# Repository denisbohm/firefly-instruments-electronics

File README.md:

# firefly-instruments-electronics
Firefly Design Test &amp; Programming Instruments Electronics

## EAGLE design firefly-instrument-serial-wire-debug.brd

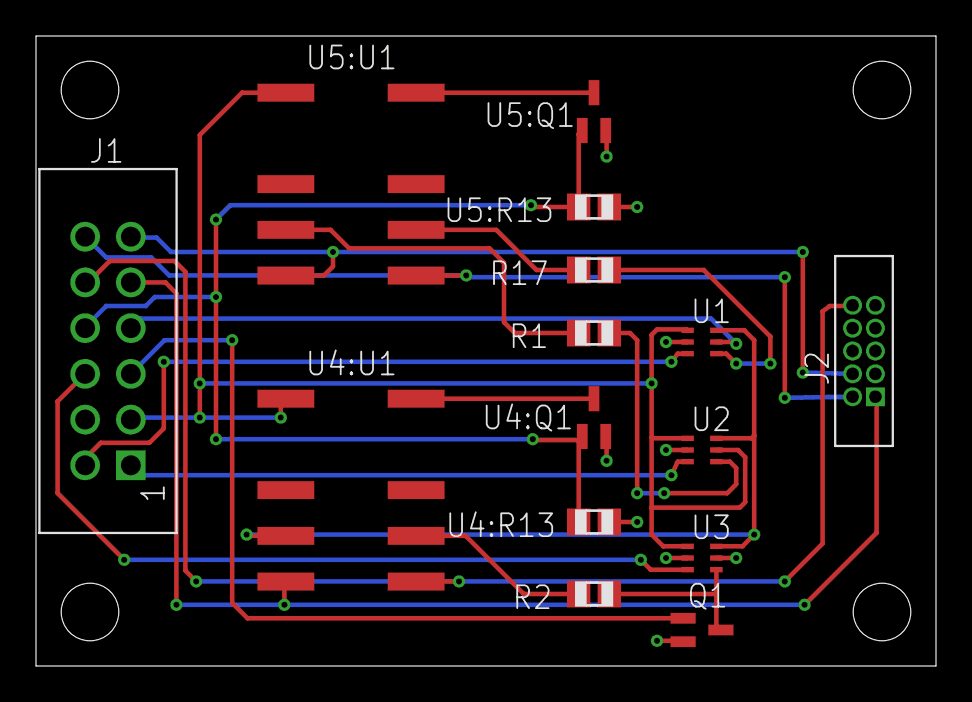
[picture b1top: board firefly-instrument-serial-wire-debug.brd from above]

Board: 2 copper layers, 50.0 x 35.0 mm, 15 parts (0 on the bottom side), 21 nets.

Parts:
J1: CON-12CON-HEADER-2X6; CON-HEADER-2X6
J2: CON-10SWD; SWD-10
Q1: FET-NMCPH3; MCPH3
R1, R2, R17: 240; R0805
U1, U2, U3: 74LVCH1T45; SOT363
U4:Q1, U5:Q1: FET-NMCPH3; MCPH3
U4:R13, U5:R13: 10K; R0805
U4:U1, U5:U1: TXS2SA

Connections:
!DUT_RESET: J1.10, J2.10, U4:U1.8
!INT_RESET: R2.2, U4:U1.9
!RESET: J1.5, Q1.1
!RESET_SENSE: J1.6, U3.3
+3V3: J1.3, U1.1, U2.1, U2.5, U3.1, U4:U1.1, U5:U1.1
DIR_TO_DUT: J1.7, U1.5
DUT_SWDCLK: J1.11, J2.4, U5:U1.5
DUT_SWDIO: J1.12, J2.2, U5:U1.8
DUT_VCC: J1.9, J2.1, U4:U1.5
EN: J1.8, U4:Q1.1, U4:R13.2, U5:Q1.1, U5:R13.2
GND: J1.4, J2.3, J2.5, Q1.2, U1.2, U2.2, U3.2, U3.5, U4:Q1.2, U4:R13.1, U5:Q1.2, U5:R13.1
INT_SWDCLK: R1.2, U5:U1.4
INT_SWDIO: R17.2, U5:U1.9
INT_VCC: U1.6, U2.6, U3.6, U4:U1.4
unnamed: Q1.3, R2.1, U3.4
unnamed: R17.1, U1.4
unnamed: R1.1, U2.4
SWDCLK: J1.1, U2.3
SWDIO: J1.2, U1.3
U4:N$2: U4:Q1.3, U4:U1.12
U5:N$2: U5:Q1.3, U5:U1.12

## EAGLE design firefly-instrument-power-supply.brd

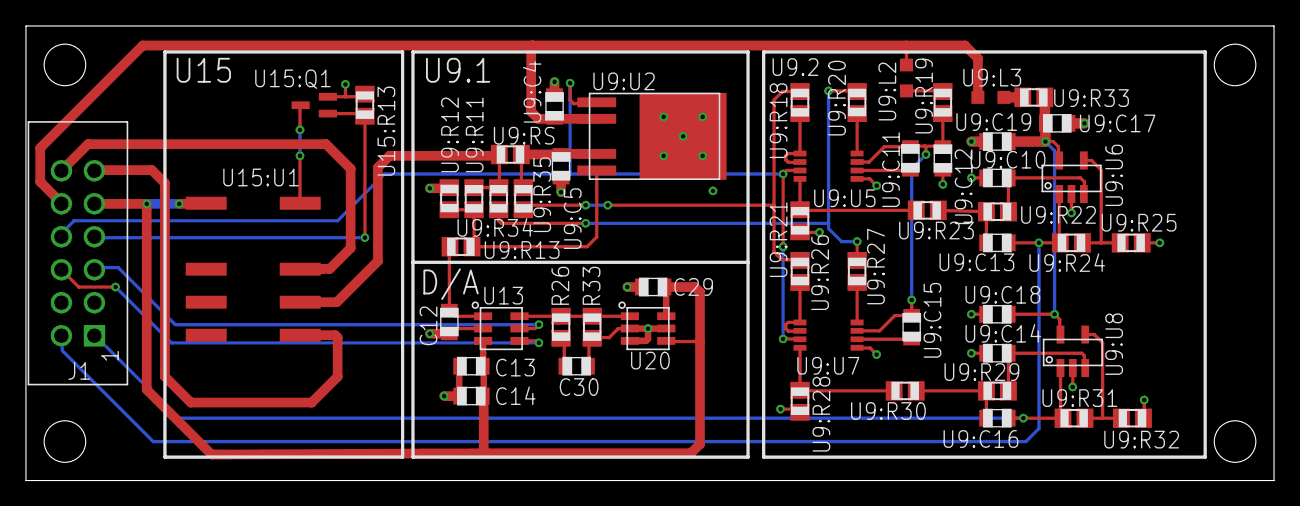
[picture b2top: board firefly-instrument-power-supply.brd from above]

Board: 2 copper layers, 96.1 x 35.0 mm, 54 parts (0 on the bottom side), 38 nets.

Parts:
C12, C13: 100nF; C0805
C14: 10uF; C0805
C29, C30: 2.2uF; C0805
J1: CON-12CON-HEADER-2X6; CON-HEADER-2X6
R26: 43; R0805
R33: 1k; R0805
U9:C4, U9:C5, U9:C17: 1uF; C0805
U9:C10, U9:C13, U9:C14, U9:C16: 1nF; C0805
U9:C11, U9:C15, U9:C18, U9:C19: 100nF; C0805
U9:C12: 10uF; C0805
U9:L2, U9:L3: 1k; L2012C
U9:R11: 650K; R0805
U9:R12, U9:R13: 100K; R0805
U9:R18: 1.8K; R0805
U9:R19, U9:R27, U9:R31, U9:R34, U9:R35: 0; R0805
U9:R20: 43; R0805
U9:R21: 12K; R0805
U9:R22, U9:R23, U9:R29, U9:R30: 10k; R0805
U9:R24: 376; R0805
U9:R25, U9:R32: 1K; R0805
U9:R26, U9:RS: 4.7; R0805
U9:R28, U15:R13: 10K; R0805
U9:R33: 1; R0805
U9:U2: VREG-ADJLDFMPT-TR; PPAK
U9:U5, U9:U7: LTC6102-1MS8; MSOP8
U9:U6, U9:U8: TLV271SN2T1G; SOT-23-5
U13: MCP47X6; SOT-23-6
U15:Q1: FET-NMCPH3; MCPH3
U15:U1: TXS2SA
U20: MCP1501; SOT-23-6

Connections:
+3V3: C13.1, C14.1, C29.1, J1.9, U13.3, U15:U1.1, U20.4, U20.6
+5V9: J1.10, U9:C4.1, U9:L2.1, U9:L3.1, U9:U2.2
ADJ: C12.1, U9:R13.1, U13.1
EN: J1.8, U9:U2.1, U9:U5.3, U9:U7.3
GND: C12.2, C13.2, C14.2, C29.2, C30.2, J1.3, J1.4, R33.2, U9:C4.2, U9:C5.2, U9:C10.2, U9:C12.2, U9:C14.2, U9:C17.2, U9:C18.2, U9:C19.2, U9:R12.1, U9:R21.2, U9:R25.2, U9:R28.2, U9:R32.2, U9:U2.TAB, U9:U5.5, U9:U6.2, U9:U7.5, U9:U8.2, U13.2, U15:Q1.2, U15:R13.1, U20.2, U20.3, U20.5
I2C_SCL: J1.5, U13.5
I2C_SDA: J1.6, U13.4
unnamed: R26.1, R33.1, U13.6, U20.1
unnamed: C30.1, R26.2
SEL: J1.7, U15:Q1.1, U15:R13.2
SHR: J1.2, U9:C13.1, U9:R24.2, U9:U6.1
SLR: J1.1, U9:C16.1, U9:R31.2, U9:U8.1
U9:N$4: U9:R11.1, U9:R12.2, U9:R13.2, U9:U2.5
U9:N$13: U9:L2.2, U9:R19.2
U9:N$14: U9:C11.1, U9:U5.6
U9:N$15: U9:R18.1, U9:U5.1, U9:U5.2
U9:N$16: U9:R20.2, U9:U5.8
U9:N$17: U9:R21.1, U9:R23.1, U9:U5.4
U9:N$18: U9:C13.2, U9:R22.1, U9:R23.2
U9:N$19: U9:C10.1, U9:R22.2, U9:U6.3
U9:N$20: U9:R24.1, U9:R25.1, U9:U6.4
U9:N$21: U9:C15.1, U9:U7.6
U9:N$22: U9:R26.1, U9:U7.1, U9:U7.2
U9:N$23: U9:R27.2, U9:U7.8
U9:N$24: U9:R28.1, U9:R30.1, U9:U7.4
U9:N$25: U9:C16.2, U9:R29.1, U9:R30.2
U9:N$26: U9:C14.1, U9:R29.2, U9:U8.3
U9:N$27: U9:R31.1, U9:R32.1, U9:U8.4
U9:N$28: U9:L3.2, U9:R33.2
U9:N$35: U9:C5.1, U9:R35.2, U9:RS.1, U9:U2.4
U9:SENSE_R: U9:R18.2, U9:R26.2, U9:R35.1
U9:SENSE_S: U9:R20.1, U9:R27.1, U9:R34.1
U9:VCSA: U9:C11.2, U9:C12.1, U9:C15.2, U9:R19.1, U9:U5.7, U9:U7.7
U9:VOA: U9:C17.1, U9:C18.1, U9:C19.1, U9:R33.1, U9:U6.5, U9:U8.5
U15:N$2: U15:Q1.3, U15:U1.12
VADJ: U9:R11.2, U9:R34.2, U9:RS.2, U15:U1.9
VADJ_NC: J1.12, U15:U1.10
VADJ_NO: J1.11, U15:U1.8

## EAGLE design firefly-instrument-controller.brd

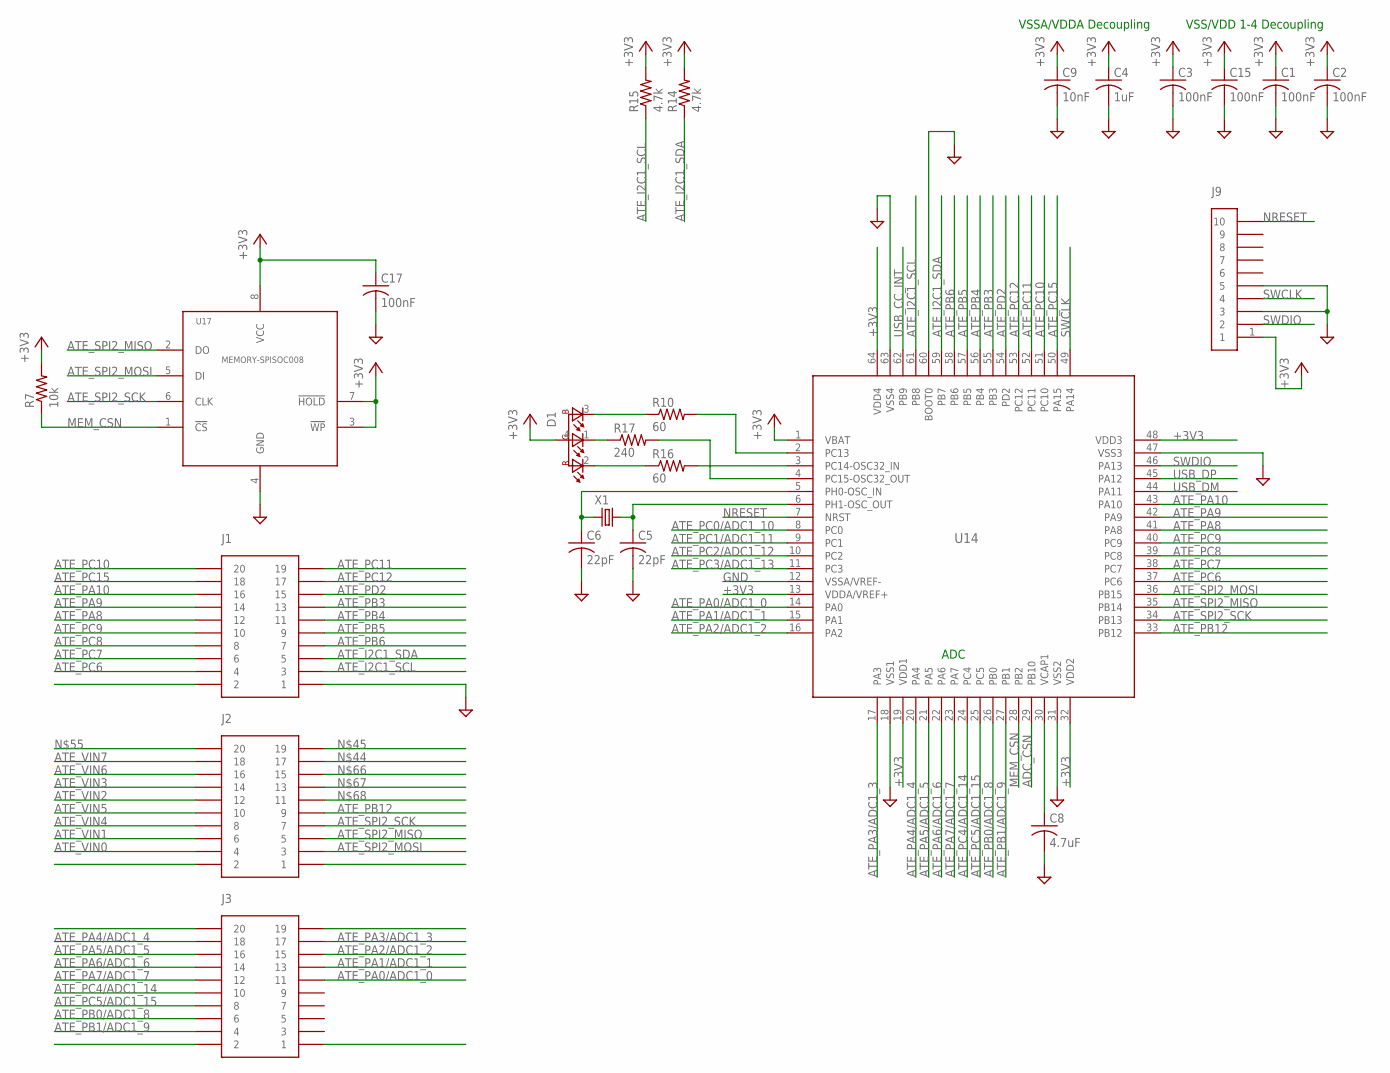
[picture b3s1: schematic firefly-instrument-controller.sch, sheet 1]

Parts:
C1, C2, C3, C15, C17: 100nF; C0805
C4: 1uF; C0805
C5, C6: 22pF; C0805
C8: 4.7uF; C0805
C9: 10nF; C0805
D1: LED-RGB-CAMSL0201RGB; MSL0201RGB
J1, J2, J3: CON-200.05"; CON-HEADER-2X10-0.05
J9: CON-10SWD; SWD-10
R7: 10k; R0805
R10, R16: 60; R0805
R14, R15: 4.7k; R0805
R17: 240; R0805
U14: STM32F411-LQFP64; LQFP-64
U17: MEMORY-SPISOC008; SOC008
X1: XTAL2TXC_7A; TXC_7A

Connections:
+3V3: C1.1, C2.1, C3.1, C4.1, C9.1, C15.1, C17.1, D1.4 (A), J9.1, R7.2, R14.2, R15.2, U14.1 (VBAT), U14.13 (VDDA/VREF+), U14.19 (VDD1), U14.32 (VDD2), U14.48 (VDD3), U14.64 (VDD4), U17.3 (!WP), U17.7 (!HOLD), U17.8 (VCC); also elsewhere on the board
ADC_CSN: U14.29 (PB10); also elsewhere on the board
ATE_I2C1_SCL: J1.3, R15.1, U14.61 (PB8); also elsewhere on the board
ATE_I2C1_SDA: J1.5, R14.1, U14.59 (PB7); also elsewhere on the board
ATE_PA0/ADC1_0: J3.11, U14.14 (PA0)
ATE_PA1/ADC1_1: J3.13, U14.15 (PA1)
ATE_PA2/ADC1_2: J3.15, U14.16 (PA2)
ATE_PA3/ADC1_3: J3.17, U14.17 (PA3)
ATE_PA4/ADC1_4: J3.18, U14.20 (PA4)
ATE_PA5/ADC1_5: J3.16, U14.21 (PA5)
ATE_PA6/ADC1_6: J3.14, U14.22 (PA6)
ATE_PA7/ADC1_7: J3.12, U14.23 (PA7)
ATE_PA8: J1.12, U14.41 (PA8)
ATE_PA9: J1.14, U14.42 (PA9)
ATE_PA10: J1.16, U14.43 (PA10)
ATE_PB0/ADC1_8: J3.6, U14.26 (PB0)
ATE_PB1/ADC1_9: J3.4, U14.27 (PB1)
ATE_PB3: J1.13, U14.55 (PB3)
ATE_PB4: J1.11, U14.56 (PB4)
ATE_PB5: J1.9, U14.57 (PB5)
ATE_PB6: J1.7, U14.58 (PB6)
ATE_PB12: J2.9, U14.33 (PB12)
ATE_PC0/ADC1_10: U14.8 (PC0)
ATE_PC1/ADC1_11: U14.9 (PC1)
ATE_PC2/ADC1_12: U14.10 (PC2)
ATE_PC3/ADC1_13: U14.11 (PC3)
ATE_PC4/ADC1_14: J3.10, U14.24 (PC4)
ATE_PC5/ADC1_15: J3.8, U14.25 (PC5)
ATE_PC6: J1.4, U14.37 (PC6)
ATE_PC7: J1.6, U14.38 (PC7)
ATE_PC8: J1.8, U14.39 (PC8)
ATE_PC9: J1.10, U14.40 (PC9)
ATE_PC10: J1.20, U14.51 (PC10)
ATE_PC11: J1.19, U14.52 (PC11)
ATE_PC12: J1.17, U14.53 (PC12)
ATE_PC15: J1.18, U14.50 (PA15)
ATE_PD2: J1.15, U14.54 (PD2)
ATE_SPI2_MISO: J2.5, U14.35 (PB14), U17.2 (DO); also elsewhere on the board
ATE_SPI2_MOSI: J2.3, U14.36 (PB15), U17.5 (DI); also elsewhere on the board
ATE_SPI2_SCK: J2.7, U14.34 (PB13), U17.6 (CLK); also elsewhere on the board
ATE_VIN0: J2.4; also elsewhere on the board
ATE_VIN1: J2.6; also elsewhere on the board
ATE_VIN2: J2.12; also elsewhere on the board
ATE_VIN3: J2.14; also elsewhere on the board
ATE_VIN4: J2.8; also elsewhere on the board
ATE_VIN5: J2.10; also elsewhere on the board
ATE_VIN6: J2.16; also elsewhere on the board
ATE_VIN7: J2.18; also elsewhere on the board
GND: C1.2, C2.2, C3.2, C4.2, C5.2, C6.2, C8.2, C9.2, C15.2, C17.2, J1.1, J9.3, J9.5, U14.12 (VSSA/VREF-), U14.18 (VSS1), U14.31 (VSS2), U14.47 (VSS3), U14.60 (BOOT0), U14.63 (VSS4), U17.4 (GND); also elsewhere on the board
MEM_CSN: R7.1, U14.28 (PB2), U17.1 (!CS)
unnamed: R10.2, U14.2 (PC13)
unnamed: C5.1, U14.6 (PH1-OSC_OUT), X1.2
unnamed: C6.1, U14.5 (PH0-OSC_IN), X1.1
unnamed: R16.2, U14.3 (PC14-OSC32_IN)
unnamed: D1.1 (G), R17.1
unnamed: D1.2 (R), R16.1
unnamed: C8.1, U14.30 (VCAP1)
unnamed: R17.2, U14.4 (PC15-OSC32_OUT)
unnamed: D1.3 (B), R10.1
NRESET: J9.10, U14.7 (NRST)
SWCLK: J9.4, U14.49 (PA14)
SWDIO: J9.2, U14.46 (PA13)
USB_CC_INT: U14.62 (PB9); also elsewhere on the board
USB_DM: U14.44 (PA11); also elsewhere on the board
USB_DP: U14.45 (PA12); also elsewhere on the board

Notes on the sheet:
ADC
VSSA/VDDA Decoupling
VSS/VDD 1-4 Decoupling

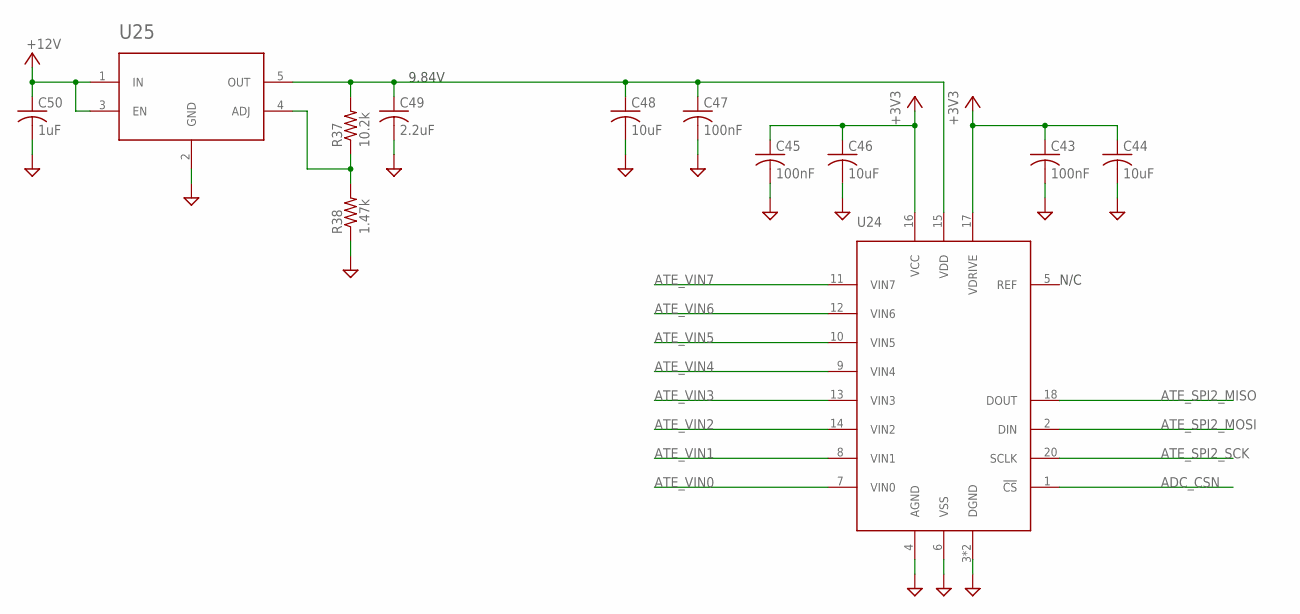
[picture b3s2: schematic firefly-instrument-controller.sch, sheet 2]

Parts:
C43, C45, C47: 100nF; C0805
C44, C46, C48: 10uF; C0805
C49: 2.2uF; C0805
C50: 1uF; C0805
R37: 10.2k; R0805
R38: 1.47k; R0805
U24: AD7327; TSSOP-20
U25: VREG-ADJAP2204; SOT-23-5

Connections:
+3V3: C43.1, C44.1, C45.1, C46.1, U24.16 (VCC), U24.17 (VDRIVE); also elsewhere on the board
+12V: C50.1, U25.1 (IN), U25.3 (EN); also elsewhere on the board
ADC_CSN: U24.1 (!CS); also elsewhere on the board
ATE_SPI2_MISO: U24.18 (DOUT); also elsewhere on the board
ATE_SPI2_MOSI: U24.2 (DIN); also elsewhere on the board
ATE_SPI2_SCK: U24.20 (SCLK); also elsewhere on the board
ATE_VIN0: U24.7 (VIN0); also elsewhere on the board
ATE_VIN1: U24.8 (VIN1); also elsewhere on the board
ATE_VIN2: U24.14 (VIN2); also elsewhere on the board
ATE_VIN3: U24.13 (VIN3); also elsewhere on the board
ATE_VIN4: U24.9 (VIN4); also elsewhere on the board
ATE_VIN5: U24.10 (VIN5); also elsewhere on the board
ATE_VIN6: U24.12 (VIN6); also elsewhere on the board
ATE_VIN7: U24.11 (VIN7); also elsewhere on the board
GND: C43.2, C44.2, C45.2, C46.2, C47.2, C48.2, C49.2, C50.2, R38.1, U24.3 (DGND), U24.4 (AGND), U24.6 (VSS), U24.19 (DGND), U25.2 (GND); also elsewhere on the board
unnamed: C47.1, C48.1, C49.1, R37.2, U24.15 (VDD), U25.5 (OUT)
unnamed: R37.1, R38.2, U25.4 (ADJ)

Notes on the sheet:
9.84V
N/C

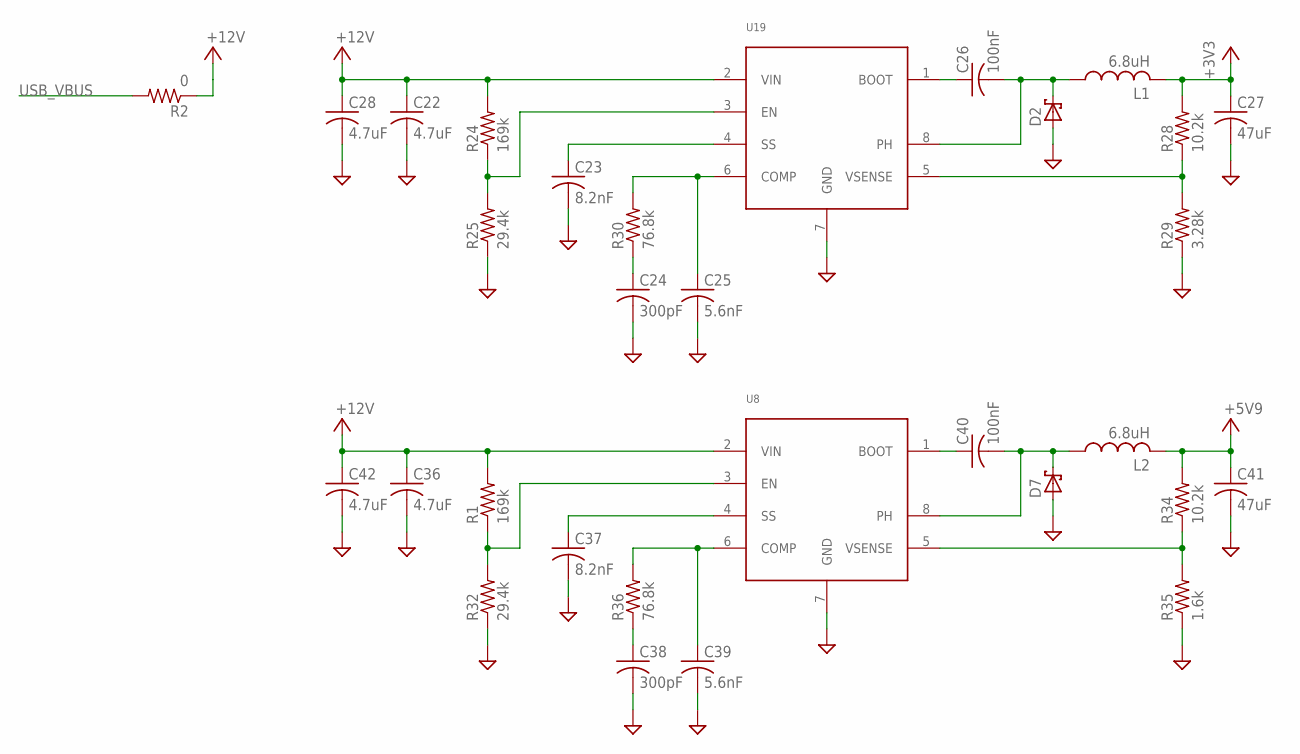
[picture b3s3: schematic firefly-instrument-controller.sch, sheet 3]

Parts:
C22, C28, C36, C42: 4.7uF; C1210
C23, C37: 8.2nF; C0805
C24, C38: 300pF; C0805
C25, C39: 5.6nF; C0805
C26, C40: 100nF; C0805
C27, C41: 47uF; C1206
D2, D7: D-USDO-214AB; DO-214AB
L1, L2: 6.8uH; SDR0805
R1, R24: 169k; R0805
R2: 0; R0805
R25, R32: 29.4k; R0805
R28, R34: 10.2k; R0805
R29: 3.28k; R0805
R30, R36: 76.8k; R0805
R35: 1.6k; R0805
U8, U19: TPS54232; R-PDSO-G8

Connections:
+3V3: C27.1, L1.2, R28.2; also elsewhere on the board
+5V9: C41.1, L2.2, R34.2
+12V: C22.1, C28.1, C36.1, C42.1, R1.2, R2.1, R24.2, U8.2 (VIN), U19.2 (VIN); also elsewhere on the board
GND: C22.2, C23.2, C24.2, C25.2, C27.2, C28.2, C36.2, C37.2, C38.2, C39.2, C41.2, C42.2, D2.A, D7.A, R25.1, R29.1, R32.1, R35.1, U8.7 (GND), U19.7 (GND); also elsewhere on the board
unnamed: C40.1, U8.1 (BOOT)
unnamed: C40.2, D7.C, L2.1, U8.8 (PH)
unnamed: C26.1, U19.1 (BOOT)
unnamed: C26.2, D2.C, L1.1, U19.8 (PH)
unnamed: R28.1, R29.2, U19.5 (VSENSE)
unnamed: C25.1, R30.2, U19.6 (COMP)
unnamed: C24.1, R30.1
unnamed: C23.1, U19.4 (SS)
unnamed: R24.1, R25.2, U19.3 (EN)
unnamed: R34.1, R35.2, U8.5 (VSENSE)
unnamed: C39.1, R36.2, U8.6 (COMP)
unnamed: C38.1, R36.1
unnamed: C37.1, U8.4 (SS)
unnamed: R1.1, R32.2, U8.3 (EN)
USB_VBUS: R2.2; also elsewhere on the board

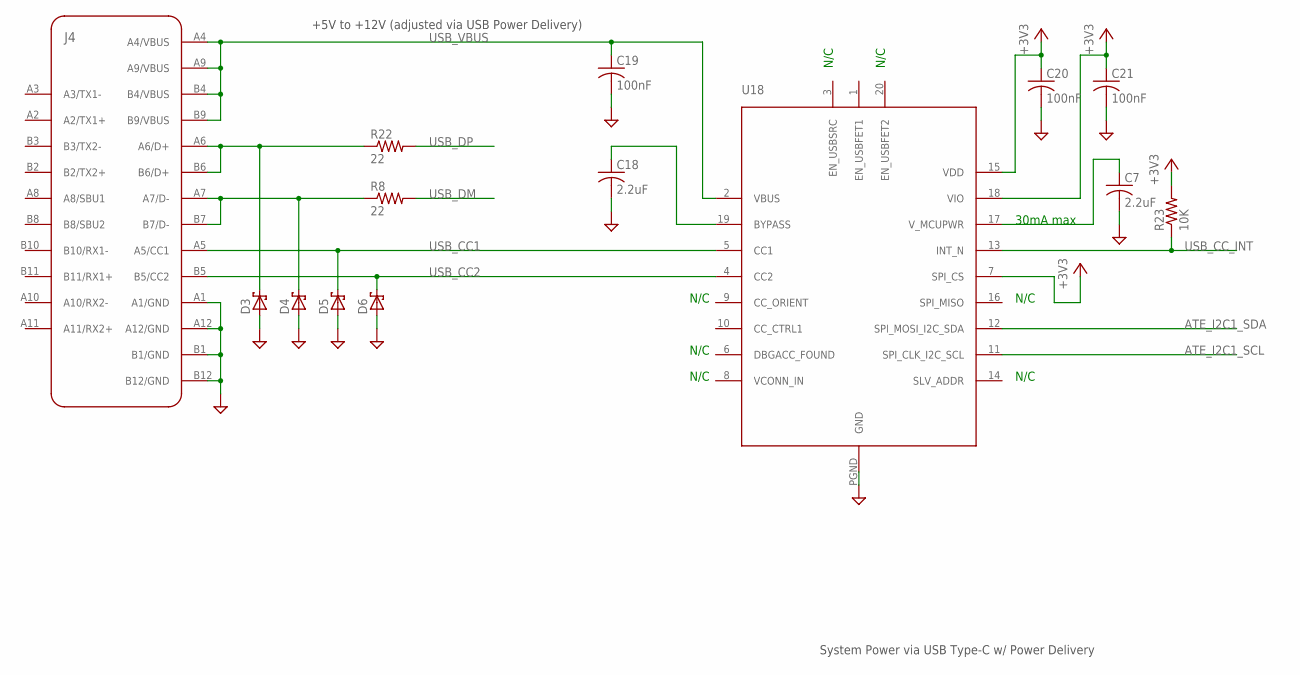
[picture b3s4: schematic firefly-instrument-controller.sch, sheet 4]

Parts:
C7, C18: 2.2uF; C0805
C19, C20, C21: 100nF; C0805
D3, D4, D5, D6: D-USSMM4FXXA; SMM4FXXA
J4: USB-CAUSB1-DFN-PTR3; AUSB1-DFN-PTR3
R8, R22: 22; R0805
R23: 10K; R0805
U18: PTN5100; HVQFN20

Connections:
+3V3: C20.1, C21.1, R23.2, U18.7 (SPI_CS), U18.15 (VDD), U18.18 (VIO); also elsewhere on the board
ATE_I2C1_SCL: U18.11 (SPI_CLK_I2C_SCL); also elsewhere on the board
ATE_I2C1_SDA: U18.12 (SPI_MOSI_I2C_SDA); also elsewhere on the board
GND: C7.2, C18.2, C19.2, C20.2, C21.2, D3.A, D4.A, D5.A, D6.A, J4.A1 (A1/GND), J4.A12 (A12/GND), J4.B1 (B1/GND), J4.B12 (B12/GND), U18.PGND (GND); also elsewhere on the board
unnamed: C18.1, U18.19 (BYPASS)
unnamed: C7.1, U18.17 (V_MCUPWR)
USBC_DM: D4.C, J4.A7 (A7/D-), J4.B7 (B7/D-), R8.1
USBC_DP: D3.C, J4.A6 (A6/D+), J4.B6 (B6/D+), R22.1
USB_CC1: D5.C, J4.A5 (A5/CC1), U18.5 (CC1)
USB_CC2: D6.C, J4.B5 (B5/CC2), U18.4 (CC2)
USB_CC_INT: R23.1, U18.13 (INT_N); also elsewhere on the board
USB_DM: R8.2; also elsewhere on the board
USB_DP: R22.2; also elsewhere on the board
USB_VBUS: C19.1, J4.A4 (A4/VBUS), J4.A9 (A9/VBUS), J4.B4 (B4/VBUS), J4.B9 (B9/VBUS), U18.2 (VBUS); also elsewhere on the board

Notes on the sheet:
N/C
30mA max
System Power via USB Type-C w/ Power Delivery
+5V to +12V (adjusted via USB Power Delivery)

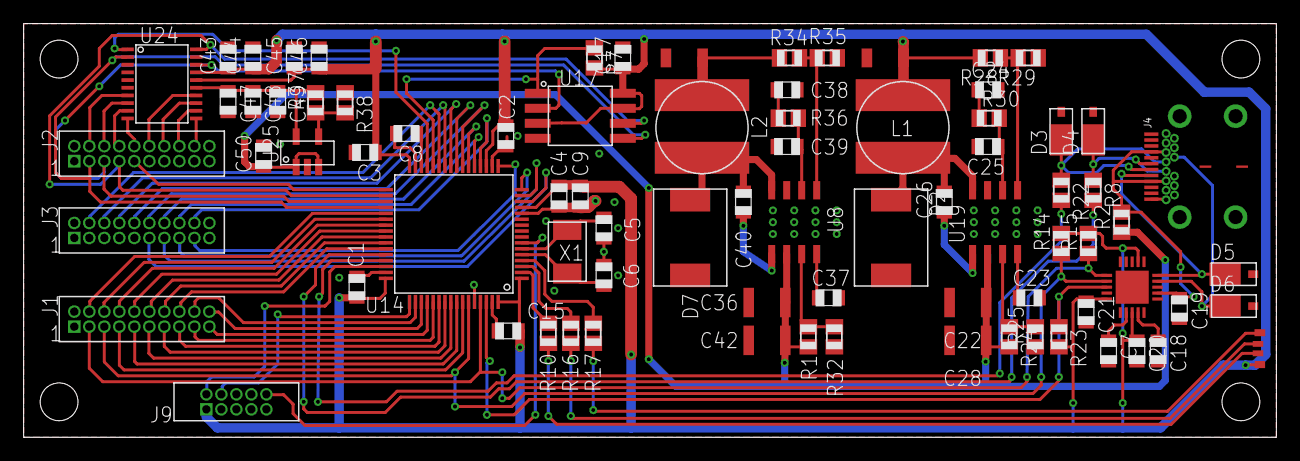
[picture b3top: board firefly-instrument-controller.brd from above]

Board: 2 copper layers, 106.0 x 35.0 mm, 81 parts (0 on the bottom side), 86 nets.

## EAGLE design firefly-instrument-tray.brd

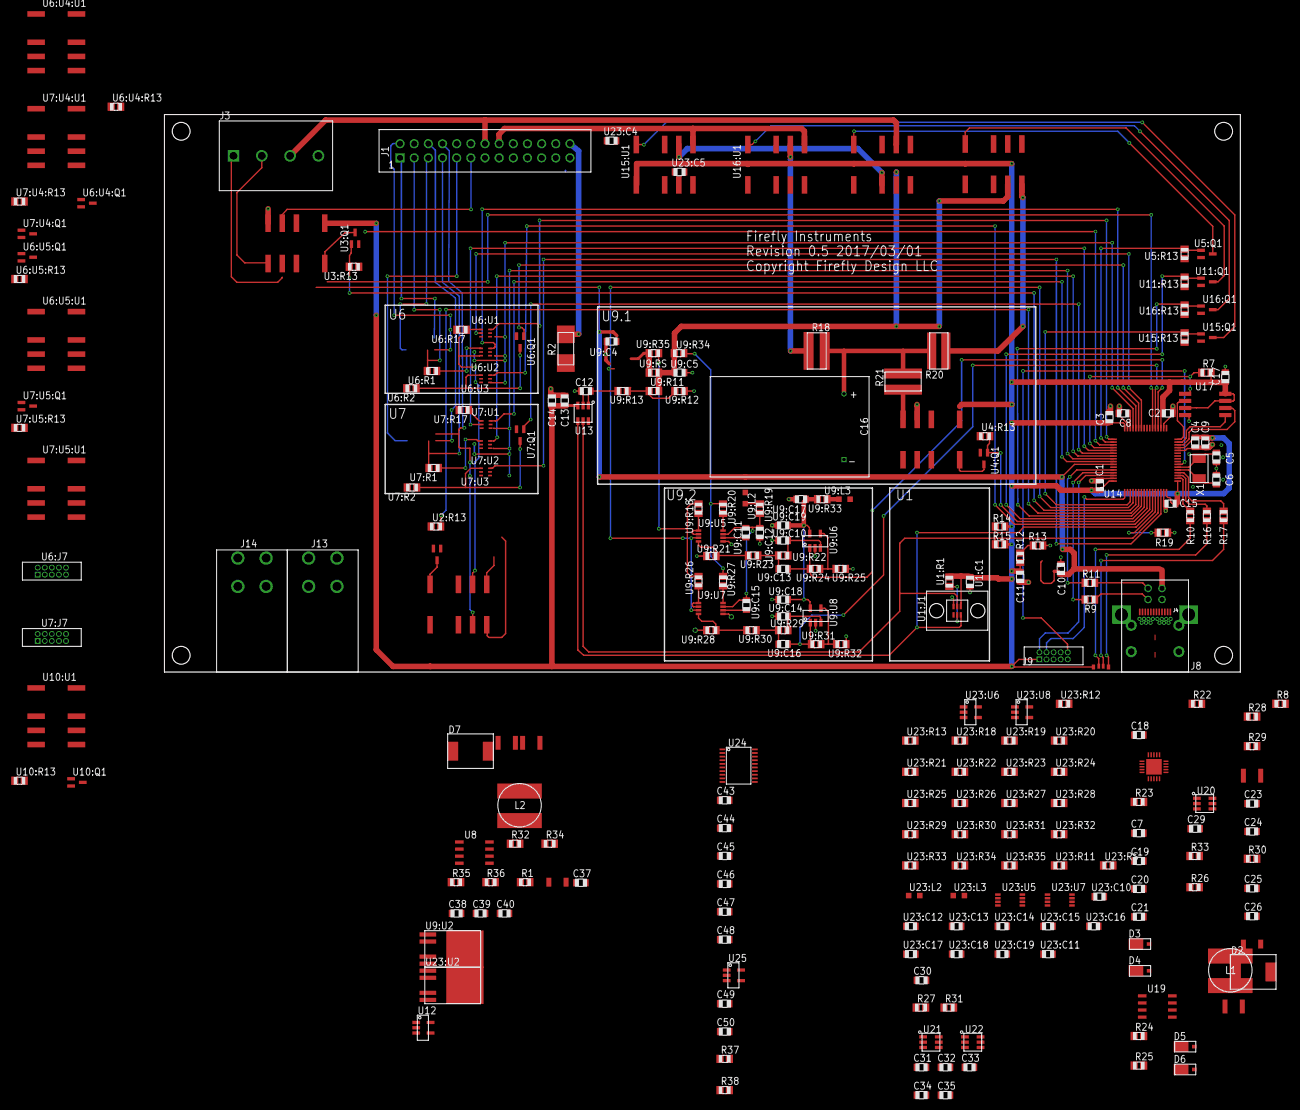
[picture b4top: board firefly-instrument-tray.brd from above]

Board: 2 copper layers, 193.0 x 100.0 mm, 251 parts (0 on the bottom side), 181 nets.

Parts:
C1, C2, C3, C12, C13, C15, C17, C19, C20, C21, C26, C31, C32, C40, C43, C45, C47: 100nF; C0805
C4, C10, C11, C50: 1uF; C0805
C5, C6: 22pF; C0805
C7, C18, C29, C30, C34, C35, C49: 2.2uF; C0805
C8: 4.7uF; C0805
C9: 10nF; C0805
C14, C33, C44, C46, C48: 10uF; C0805
C16: 1F; PM118
C22, C28, C36, C42: 4.7uF; C1210
C23, C37: 8.2nF; C0805
C24, C38: 300pF; C0805
C25, C39: 5.6nF; C0805
C27, C41: 47uF; C1206
D1: LED-RGB-CAMSL0201RGB; MSL0201RGB
D2, D7: D-USDO-214AB; DO-214AB
D3, D4, D5, D6: D-USSMM4FXXA; SMM4FXXA
J1: CON-26; CON-HEADER-2X13
J3: CON-4282847-4; 282847-4
J4: USB-CAUSB1-DFN-PTR3; AUSB1-DFN-PTR3
J8: USB-4PINUSB-B1HSB6; USB-B1HSB6
J9: CON-10SWD; SWD-10
J13, J14: CON-1CT3151; CT3151
L1, L2: 6.8uH; SDR0805
R1, R24: 169k; R0805
R2: 100; RW0S6BB
R7: 10k; R0805
R8, R9, R11, R22: 22; R0805
R10, R16: 60; R0805
R12: 72.5k; R0805
R13, R23: 10K; R0805
R14, R15: 4.7k; R0805
R17: 240; R0805
R18: 1 (2W WW); RCL1225
R19: 0; R0805
R20: 49.9 (2W WW); KRL6432
R21: 49.9 (2W WW); RCL1225
R25, R32: 29.4k; R0805
R26, R31: 43; R0805
R27, R33: 1; R0805
R28, R34, R37: 10.2k; R0805
R29: 3.28k; R0805
R30, R36: 76.8k; R0805
R35: 1.6k; R0805
R38: 1.47k; R0805
U1:C1, U9:C4, U9:C5, U9:C17, U23:C4, U23:C5, U23:C17: 1uF; C0805
U1:J1: SMFLP
U1:R1, U9:R22, U9:R23, U9:R29, U9:R30, U23:R22, U23:R23, U23:R29, U23:R30: 10k; R0805
U1:U1: TCS3471; DFN6
U2:Q1, U3:Q1, U4:Q1, U5:Q1, U6:Q1, U6:U4:Q1, U6:U5:Q1, U7:Q1, U7:U4:Q1, U7:U5:Q1, U10:Q1, U11:Q1, U15:Q1, U16:Q1: FET-NMCPH3; MCPH3
U2:R13, U3:R13, U4:R13, U5:R13, U6:U4:R13, U6:U5:R13, U7:U4:R13, U7:U5:R13, U9:R28, U10:R13, U11:R13, U15:R13, U16:R13, U23:R28: 10K; R0805
U2:U1, U3:U1, U4:U1, U5:U1, U6:U4:U1, U6:U5:U1, U7:U4:U1, U7:U5:U1, U10:U1, U11:U1, U15:U1, U16:U1: TXS2SA
U6:J7, U7:J7: CON-10SWD; SWD-10
U6:R1, U6:R2, U6:R17, U7:R1, U7:R2, U7:R17: 240; R0805
U6:U1, U6:U2, U6:U3, U7:U1, U7:U2, U7:U3: 74LVCH1T45; SOT363
U8, U19: TPS54232; R-PDSO-G8
U9:C10, U9:C13, U9:C14, U9:C16, U23:C10, U23:C13, U23:C14, U23:C16: 1nF; C0805
U9:C11, U9:C15, U9:C18, U9:C19, U23:C11, U23:C15, U23:C18, U23:C19: 100nF; C0805
U9:C12, U23:C12: 10uF; C0805
U9:L2, U9:L3, U23:L2, U23:L3: 1k; L2012C
U9:R11, U23:R11: 650K; R0805
U9:R12, U9:R13, U23:R12, U23:R13: 100K; R0805
U9:R18, U23:R18: 1.8K; R0805
U9:R19, U9:R27, U9:R31, U9:R34, U9:R35, U23:R19, U23:R27, U23:R31, U23:R34, U23:R35: 0; R0805
U9:R20, U23:R20: 43; R0805
U9:R21, U23:R21: 12K; R0805
U9:R24, U23:R24: 376; R0805
U9:R25, U9:R32, U23:R25, U23:R32: 1K; R0805
U9:R26, U9:RS, U23:R26, U23:RS: 4.7; R0805
U9:R33, U23:R33: 1; R0805
U9:U2, U23:U2: VREG-ADJLDFMPT-TR; PPAK
U9:U5, U9:U7, U23:U5, U23:U7: LTC6102-1MS8; MSOP8
U9:U6, U9:U8, U23:U6, U23:U8: TLV271SN2T1G; SOT-23-5
U12: VREG-ADJAP7331-WG-7; SOT-23-5
U13, U21: MCP47X6; SOT-23-6
U14: STM32F411-LQFP64; LQFP-64
U17: MEMORY-SPISOC008; SOC008
U18: PTN5100; HVQFN20
U20, U22: MCP1501; SOT-23-6
U24: AD7327; TSSOP-20
U25: VREG-ADJAP2204; SOT-23-5
X1: XTAL2TXC_7A; TXC_7A

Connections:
+3V3: C1.1, C2.1, C3.1, C4.1, C9.1, C11.1, C13.1, C14.1, C15.1, C17.1, C20.1, C21.1, C27.1, C29.1, C32.1, C33.1, C34.1, C43.1, C44.1, C45.1, C46.1, D1.4, J9.1, L1.2, R7.2, R12.2, R14.2, R15.2, R23.2, R28.2, U1:C1.1, U1:R1.2, U1:U1.1, U2:U1.1, U3:U1.1, U4:U1.1, U5:U1.1, U6:U1.1, U6:U2.1, U6:U2.5, U6:U3.1, U6:U4:U1.1, U6:U5:U1.1, U7:U1.1, U7:U2.1, U7:U2.5, U7:U3.1, U7:U4:U1.1, U7:U5:U1.1, U10:U1.1, U11:U1.1, U12.5, U13.3, U14.1, U14.13, U14.19, U14.32, U14.48, U14.64, U15:U1.1, U16:U1.1, U17.3, U17.7, U17.8, U18.7, U18.15, U18.18, U20.4, U20.6, U21.3, U22.4, U22.6, U24.16, U24.17
+5V9: C41.1, L2.2, R34.2, U9:C4.1, U9:L2.1, U9:L3.1, U9:U2.2, U23:C4.1, U23:L2.1, U23:L3.1, U23:U2.2
+12V: C22.1, C28.1, C36.1, C42.1, C50.1, J13.1, J13.2, J13.3, J13.4, R1.2, R24.2, U8.2, U19.2, U25.1, U25.3
ADC_CSN: U14.43, U24.1
ATE_BAT_ADJ_EN: U14.51, U15:Q1.1, U15:R13.2
ATE_BAT_CAP_EN: U14.55, U16:Q1.1, U16:R13.2
ATE_BS_ADJ: C12.1, U9:R13.1, U13.1
ATE_BS_EN: U9:U2.1, U9:U5.3, U9:U7.3, U14.52
ATE_BS_SHR: U9:C13.1, U9:R24.2, U9:U6.1, U14.20
ATE_BS_SLR: U9:C16.1, U9:R31.2, U9:U8.1, U14.21
ATE_BUTTON+: U10:U1.8, U24.10
ATE_BUTTON_EN: U3:Q1.1, U3:R13.2, U14.53
ATE_DRAIN_EN: U4:Q1.1, U4:R13.2, U14.57
ATE_FILL_EN: U11:Q1.1, U11:R13.2, U14.56
ATE_MCU1_VCC: U2:U1.8, U24.14
ATE_MCU2_VCC: U2:U1.5, U24.13
ATE_SWD1_DIR_TO_DUT: U6:U1.5, U14.26
ATE_SWD1_NRESET: U6:Q1.1, U14.27
ATE_SWD1_PWR: U6:U4:Q1.1, U6:U4:R13.2, U6:U5:Q1.1, U6:U5:R13.2, U14.29
ATE_SWD1_SENSE_NRESET: U6:U3.3, U14.58
ATE_SWD1_SWDCLK: U6:U2.3, U14.28
ATE_SWD1_SWDIO: U6:U1.3, U14.33
ATE_SWD2_DIR_TO_DUT: U7:U1.5, U14.37
ATE_SWD2_NRESET: U7:Q1.1, U14.38
ATE_SWD2_PWR: U7:U4:Q1.1, U7:U4:R13.2, U7:U5:Q1.1, U7:U5:R13.2, U14.40
ATE_SWD2_SENSE_NRESET: U7:U3.3, U14.62
ATE_SWD2_SWDCLK: U7:U2.3, U14.39
ATE_SWD2_SWDIO: U7:U1.3, U14.41
ATE_USB_5V_EN: U5:Q1.1, U5:R13.2, U14.34
ATE_USB_ADJ: C31.1, U21.1, U23:R13.1
ATE_USB_EN: U14.35, U23:U2.1, U23:U5.3, U23:U7.3
ATE_USB_SHR: U14.22, U23:C13.1, U23:R24.2, U23:U6.1
ATE_USB_SLR: U14.23, U23:C16.1, U23:R31.2, U23:U8.1
ATE_VB: U10:U1.5, U24.9
ATE_VSENSE: U2:Q1.1, U2:R13.2, U10:Q1.1, U10:R13.2, U14.54
BATADJ: U9:C5.1, U9:R11.2, U9:R34.2, U9:RS.2, U11:U1.4, U15:U1.9, U24.7
BATCAP: R18.1, U16:U1.9
BATCAPV: C16.+, R18.2, R20.2, R21.2, U24.11
BOOT0: R19.1, U14.60
DRAINCAP: R21.1, U4:U1.5
DUT_BATTERY+: J1.16, U15:U1.8, U16:U1.8
DUT_BUTTON+: J1.11, J3.1, U3:U1.4, U10:U1.9
DUT_BUTTON-: J1.23, J3.2, U3:U1.5
DUT_MCU1_NRESET: J1.5, U6:J7.10, U6:U4:U1.8
DUT_MCU1_SWDCLK: J1.3, U6:J7.4, U6:U5:U1.5
DUT_MCU1_SWDIO: J1.2, U6:J7.2, U6:U5:U1.8
DUT_MCU1_VCC: J1.1, U2:U1.9, U6:J7.1, U6:U4:U1.5
DUT_MCU2_NRESET: J1.9, U7:J7.10, U7:U4:U1.8
DUT_MCU2_SWDCLK: J1.7, U7:J7.4, U7:U5:U1.5
DUT_MCU2_SWDIO: J1.6, U7:J7.2, U7:U5:U1.8
DUT_MCU2_VCC: J1.8, U2:U1.4, U7:J7.1, U7:U4:U1.5
DUT_MOTOR+: J1.26, R2.1
DUT_MOTOR-: J1.25, R2.2
DUT_USB_5V: J1.14, J3.3, U5:U1.9
DUT_VB: J1.15, U10:U1.4
FILLCAP: R20.1, U11:U1.5
GND: C1.2, C2.2, C3.2, C4.2, C5.2, C6.2, C7.2, C8.2, C9.2, C10.2, C11.2, C12.2, C13.2, C14.2, C15.2, C16.-, C17.2, C18.2, C19.2, C20.2, C21.2, C22.2, C23.2, C24.2, C25.2, C27.2, C28.2, C29.2, C30.2, C31.2, C32.2, C33.2, C34.2, C35.2, C36.2, C37.2, C38.2, C39.2, C41.2, C42.2, C43.2, C44.2, C45.2, C46.2, C47.2, C48.2, C49.2, C50.2, D2.A, D3.A, D4.A, D5.A, D6.A, D7.A, J1.4, J1.24, J3.4, J4.A1, J4.A12, J4.B1, J4.B12, J8.4, J9.3, J9.5, J14.1, J14.2, J14.3, J14.4, R13.1, R19.2, R25.1, R27.2, R29.1, R32.1, R33.2, R35.1, R38.1, U1:C1.2, U1:U1.3, U2:Q1.2, U2:R13.1, U3:Q1.2, U3:R13.1, U4:Q1.2, U4:R13.1, U4:U1.4, U5:Q1.2, U5:R13.1, U6:J7.3, U6:J7.5, U6:Q1.2, U6:U1.2, U6:U2.2, U6:U3.2, U6:U3.5, U6:U4:Q1.2, U6:U4:R13.1, U6:U5:Q1.2, U6:U5:R13.1, U7:J7.3, U7:J7.5, U7:Q1.2, U7:U1.2, U7:U2.2, U7:U3.2, U7:U3.5, U7:U4:Q1.2, U7:U4:R13.1, U7:U5:Q1.2, U7:U5:R13.1, U8.7, U9:C4.2, U9:C5.2, U9:C10.2, U9:C12.2, U9:C14.2, U9:C17.2, U9:C18.2, U9:C19.2, U9:R12.1, U9:R21.2, U9:R25.2, U9:R28.2, U9:R32.2, U9:U2.TAB, U9:U5.5, U9:U6.2, U9:U7.5, U9:U8.2, U10:Q1.2, U10:R13.1, U11:Q1.2, U11:R13.1, U12.2, U13.2, U14.12, U14.18, U14.31, U14.47, U14.63, U15:Q1.2, U15:R13.1, U16:Q1.2, U16:R13.1, U17.4, U18.PGND, U19.7, U20.2, U20.3, U20.5, U21.2, U22.2, U22.3, U22.5, U23:C4.2, U23:C5.2, U23:C10.2, U23:C12.2, U23:C14.2, U23:C17.2, U23:C18.2, U23:C19.2, U23:R12.1, U23:R21.2, U23:R25.2, U23:R28.2, U23:R32.2, U23:U2.TAB, U23:U5.5, U23:U6.2, U23:U7.5, U23:U8.2, U24.3, U24.4, U24.6, U24.19, U25.2
I2C_SCL: R15.1, U1:U1.2, U13.5, U14.61, U18.11, U21.5
I2C_SDA: R14.1, U1:U1.6, U13.4, U14.59, U18.12, U21.4
MEM_CSN: R7.1, U14.36, U17.1
unnamed: R10.2, U14.2
unnamed: C40.1, U8.1
unnamed: C40.2, D7.C, L2.1, U8.8
unnamed: C19.1, J4.A4, J4.A9, J4.B4, J4.B9, U18.2
unnamed: C5.1, U14.6, X1.2
unnamed: C6.1, U14.5, X1.1
unnamed: R16.2, U14.3
unnamed: C8.1, U14.30
unnamed: R12.1, R13.2, U12.4
unnamed: J8.2, R11.2
unnamed: R17.2, U14.4
unnamed: J8.3, R9.2
unnamed: D1.3, R10.1
unnamed: D1.1, R16.1
unnamed: D1.2, R17.1
unnamed: D3.C, J4.A6, J4.B6, R22.1
unnamed: D4.C, J4.A7, J4.B7, R8.1
unnamed: D5.C, J4.A5, U18.5
unnamed: D6.C, J4.B5, U18.4
unnamed: R26.1, R33.1, U13.6, U20.1
unnamed: C18.1, U18.19
unnamed: C7.1, U18.17
unnamed: C26.1, U19.1
unnamed: C26.2, D2.C, L1.1, U19.8
unnamed: C30.1, R26.2
unnamed: R28.1, R29.2, U19.5
unnamed: C25.1, R30.2, U19.6
unnamed: C24.1, R30.1
unnamed: C23.1, U19.4
unnamed: R24.1, R25.2, U19.3
unnamed: R27.1, R31.1, U21.6, U22.1
unnamed: C35.1, R31.2
unnamed: R34.1, R35.2, U8.5
unnamed: C39.1, R36.2, U8.6
unnamed: C38.1, R36.1
unnamed: C37.1, U8.4
unnamed: R1.1, R32.2, U8.3
unnamed: C47.1, C48.1, C49.1, R37.2, U24.15, U25.5
unnamed: R37.1, R38.2, U25.4
NRESET: J9.10, U14.7
SPI_MISO: U14.16, U17.2, U24.18
SPI_MOSI: U14.15, U17.5, U24.2
SPI_SCLK: U14.14, U17.6, U24.20
SWCLK: J9.4, U14.49
SWDIO: J9.2, U14.46
U1:INT: U1:R1.1, U1:U1.5
U2:N$2: U2:Q1.3, U2:U1.12
U3:N$2: U3:Q1.3, U3:U1.12
U4:N$2: U4:Q1.3, U4:U1.12
U5:N$2: U5:Q1.3, U5:U1.12
U6:INT_NRESET: U6:R2.2, U6:U4:U1.9
U6:INT_SWDCLK: U6:R1.2, U6:U5:U1.4
U6:INT_SWDIO: U6:R17.2, U6:U5:U1.9
U6:INT_VCC: U6:U1.6, U6:U2.6, U6:U3.6, U6:U4:U1.4
U6:N$1: U6:Q1.3, U6:R2.1, U6:U3.4
U6:N$2: U6:R17.1, U6:U1.4
U6:N$3: U6:R1.1, U6:U2.4
U6:U4:N$2: U6:U4:Q1.3, U6:U4:U1.12
U6:U5:N$2: U6:U5:Q1.3, U6:U5:U1.12
U7:INT_NRESET: U7:R2.2, U7:U4:U1.9
U7:INT_SWDCLK: U7:R1.2, U7:U5:U1.4
U7:INT_SWDIO: U7:R17.2, U7:U5:U1.9
U7:INT_VCC: U7:U1.6, U7:U2.6, U7:U3.6, U7:U4:U1.4
U7:N$1: U7:Q1.3, U7:R2.1, U7:U3.4
U7:N$2: U7:R17.1, U7:U1.4
U7:N$3: U7:R1.1, U7:U2.4
U7:U4:N$2: U7:U4:Q1.3, U7:U4:U1.12
U7:U5:N$2: U7:U5:Q1.3, U7:U5:U1.12
U9:N$4: U9:R11.1, U9:R12.2, U9:R13.2, U9:U2.5
U9:N$13: U9:L2.2, U9:R19.2
U9:N$14: U9:C11.1, U9:U5.6
U9:N$15: U9:R18.1, U9:U5.1, U9:U5.2
U9:N$16: U9:R20.2, U9:U5.8
U9:N$17: U9:R21.1, U9:R23.1, U9:U5.4
U9:N$18: U9:C13.2, U9:R22.1, U9:R23.2
U9:N$19: U9:C10.1, U9:R22.2, U9:U6.3
U9:N$20: U9:R24.1, U9:R25.1, U9:U6.4
U9:N$21: U9:C15.1, U9:U7.6
U9:N$22: U9:R26.1, U9:U7.1, U9:U7.2
U9:N$23: U9:R27.2, U9:U7.8
U9:N$24: U9:R28.1, U9:R30.1, U9:U7.4
U9:N$25: U9:C16.2, U9:R29.1, U9:R30.2
U9:N$26: U9:C14.1, U9:R29.2, U9:U8.3
U9:N$27: U9:R31.1, U9:R32.1, U9:U8.4
U9:N$28: U9:L3.2, U9:R33.2
U9:N$35: U9:R35.2, U9:RS.1, U9:U2.4
U9:SENSE_R: U9:R18.2, U9:R26.2, U9:R35.1
U9:SENSE_S: U9:R20.1, U9:R27.1, U9:R34.1
U9:VCSA: U9:C11.2, U9:C12.1, U9:C15.2, U9:R19.1, U9:U5.7, U9:U7.7
U9:VOA: U9:C17.1, U9:C18.1, U9:C19.1, U9:R33.1, U9:U6.5, U9:U8.5
U10:N$2: U10:Q1.3, U10:U1.12
U11:N$2: U11:Q1.3, U11:U1.12
U15:N$2: U15:Q1.3, U15:U1.12
U16:N$2: U16:Q1.3, U16:U1.12
U23:N$4: U23:R11.1, U23:R12.2, U23:R13.2, U23:U2.5
U23:N$13: U23:L2.2, U23:R19.2
U23:N$14: U23:C11.1, U23:U5.6
U23:N$15: U23:R18.1, U23:U5.1, U23:U5.2
U23:N$16: U23:R20.2, U23:U5.8
U23:N$17: U23:R21.1, U23:R23.1, U23:U5.4
U23:N$18: U23:C13.2, U23:R22.1, U23:R23.2
U23:N$19: U23:C10.1, U23:R22.2, U23:U6.3
U23:N$20: U23:R24.1, U23:R25.1, U23:U6.4
U23:N$21: U23:C15.1, U23:U7.6
U23:N$22: U23:R26.1, U23:U7.1, U23:U7.2
U23:N$23: U23:R27.2, U23:U7.8
U23:N$24: U23:R28.1, U23:R30.1, U23:U7.4
U23:N$25: U23:C16.2, U23:R29.1, U23:R30.2
U23:N$26: U23:C14.1, U23:R29.2, U23:U8.3
U23:N$27: U23:R31.1, U23:R32.1, U23:U8.4
U23:N$28: U23:L3.2, U23:R33.2
U23:N$35: U23:R35.2, U23:RS.1, U23:U2.4
U23:SENSE_R: U23:R18.2, U23:R26.2, U23:R35.1
U23:SENSE_S: U23:R20.1, U23:R27.1, U23:R34.1
U23:VCSA: U23:C11.2, U23:C12.1, U23:C15.2, U23:R19.1, U23:U5.7, U23:U7.7
U23:VOA: U23:C17.1, U23:C18.1, U23:C19.1, U23:R33.1, U23:U6.5, U23:U8.5
USBADJ: U5:U1.8, U23:C5.1, U23:R11.2, U23:R34.2, U23:RS.2, U24.8
USB_CC_INT: R23.1, U14.17, U18.13
USB_DM: R8.2, R11.1, U14.44
USB_DP: R9.1, R22.2, U14.45
USB_VBUS: C10.1, J8.1, U12.1, U12.3, U14.42

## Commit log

2017-06-28 start changes to multiple boards and usb type-c

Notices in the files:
firefly-instrument-power-supply.brd:
Copyright Firefly Design LLC
